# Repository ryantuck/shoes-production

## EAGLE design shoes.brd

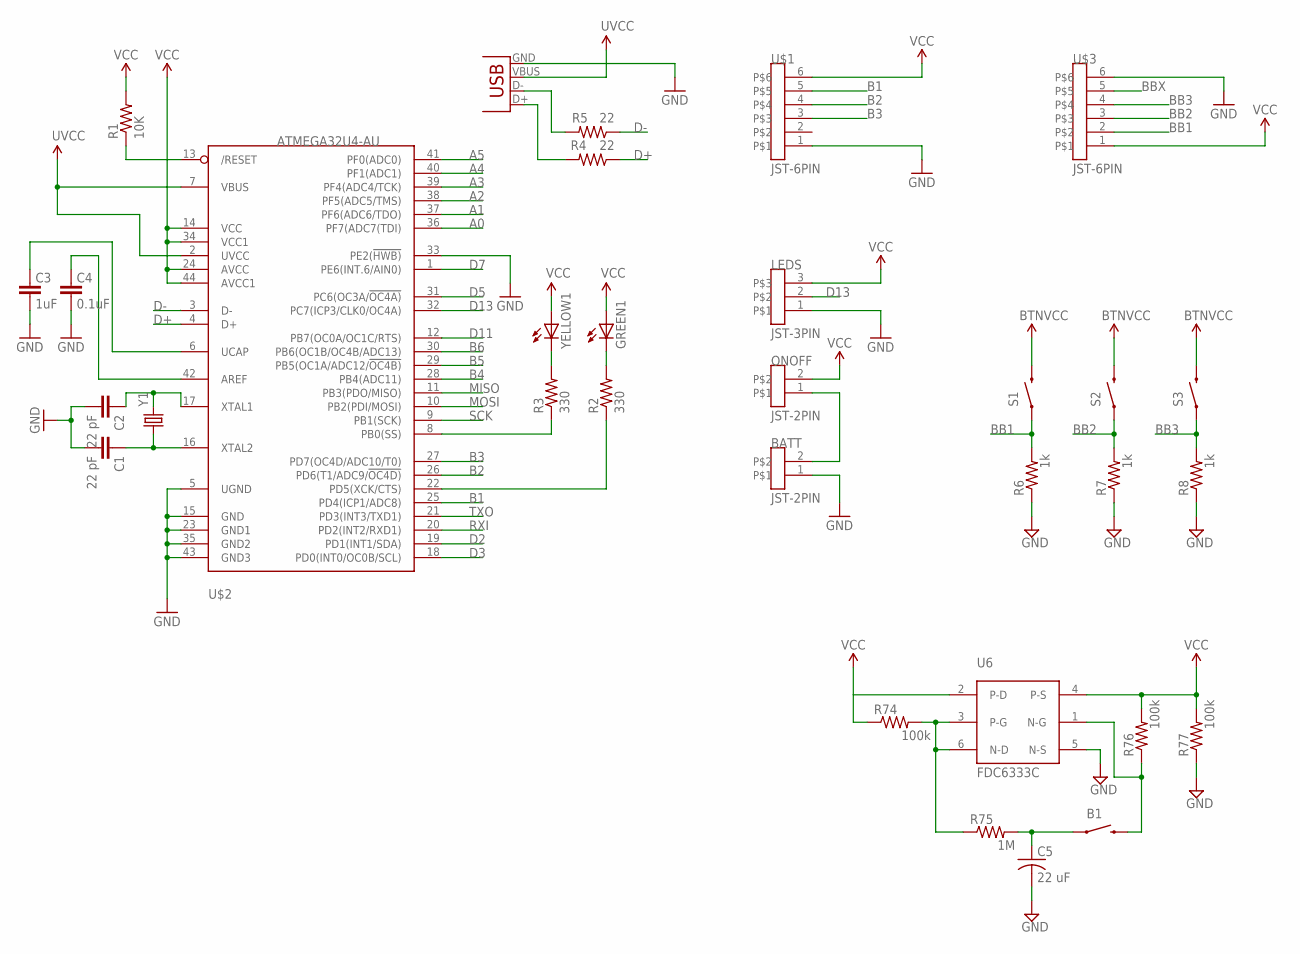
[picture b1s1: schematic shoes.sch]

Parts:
B1: SWITCH-MOMENTARY-2GULLWING; BUTTON-GULLWING
BATT: JST-2PIN; JST-PH-2
C1, C2: 22 pF; 0805
C3: 1uF; 0805
C4: 0.1uF; 0805
C5: 22 uF; 1206_P
GREEN1: LED; 0805_P
LEDS: JST-3PIN; JST-PH-3
ONOFF: JST-2PIN; JST-PH-2
R1: 10K; 0805
R2, R3: 330; 0805
R4, R5: 22; 0805
R6, R7, R8: 1k; 0805
R74, R76, R77: 100k; 0603
R75: 1M; 0603
S1, S2, S3: SWITCH-MOMENTARY-2GULLWING; BUTTON-GULLWING
U6: FDC6333C; SOT-23
U$1, U$3: JST-6PIN; JST-PH-6
U$2: ATMEGA32U4-AU; TQFP44
X2: USB-MICROB
Y1: CRYSTALHC49US; HC49US
YELLOW1: LED; 0805_P

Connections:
3.3V: R76.2, R77.2, U6.4 (P-S)
5V: GREEN1.NEG (A), LEDS.3, ONOFF.2, R1.2, U$1.6, U$2.14 (VCC), U$2.24 (AVCC), U$2.34 (VCC1), U$2.44 (AVCC1), YELLOW1.NEG (A)
A0: U$2.36 (PF7(ADC7(TDI))
A1: U$2.37 (PF6(ADC6/TDO))
A2: U$2.38 (PF5(ADC5/TMS))
A3: U$2.39 (PF4(ADC4/TCK))
A4: U$2.40 (PF1(ADC1))
A5: U$2.41 (PF0(ADC0))
B1: U$1.5, U$2.25 (PD4(ICP1/ADC8))
B2: U$1.4, U$2.26 (PD6(T1/ADC9/!OC4D))
B3: U$1.3, U$2.27 (PD7(OC4D/ADC10/T0))
B4: U$2.28 (PB4(ADC11))
B5: U$2.29 (PB5(OC1A/ADC12/!OC4B))
B6: U$2.30 (PB6(OC1B/OC4B/ADC13))
BB1: R6.POS (2), S1.A1 (1), U$3.2
BB2: R7.POS (2), S2.A1 (1), U$3.3
BB3: R8.POS (2), S3.A1 (1), U$3.4
BBX: U$3.5
BTNGND: R6.NEG (1), R7.NEG (1), R8.NEG (1), U$3.6
BTNVCC: S1.B1 (2), S2.B1 (2), S3.B1 (2), U$3.1
D2: U$2.19 (PD1(INT1/SDA))
D3: U$2.18 (PD0(INT0/OC0B/SCL))
D5: U$2.31 (PC6(OC3A/!OC4A))
D7: U$2.1 (PE6(INT.6/AIN0))
D11: U$2.12 (PB7(OC0A/OC1C/RTS))
D13: LEDS.2, U$2.32 (PC7(ICP3/CLK0/OC4A))
D14: R3.1, U$2.8 (PB0(SS))
D+: R4.1, U$2.4 (D+)
D-: R5.1, U$2.3 (D-)
GND: BATT.1, C1.POS (2), C2.POS (2), C3.1, C4.1, C5.2 (NEG), LEDS.1, R77.1, U6.5 (N-S), U$1.1, U$2.5 (UGND), U$2.15 (GND), U$2.23 (GND1), U$2.33 (PE2(!HWB)), U$2.35 (GND2), U$2.43 (GND3), X2.GND
MISO: U$2.11 (PB3(PDO/MISO))
MOSI: U$2.10 (PB2(PDI/MOSI))
unnamed: C2.NEG (1), U$2.17 (XTAL1), Y1.2
unnamed: R4.2, X2.D+
unnamed: R5.2, X2.D-
unnamed: C1.NEG (1), U$2.16 (XTAL2), Y1.1
unnamed: C4.2, U$2.42 (AREF)
unnamed: C3.2, U$2.6 (UCAP)
unnamed: R3.2, YELLOW1.POS (C)
unnamed: GREEN1.POS (C), R2.2
unnamed: B1.B1 (2), R76.1, U6.1 (N-G)
unnamed: R74.2, R75.1, U6.3 (P-G), U6.6 (N-D)
unnamed: B1.A1 (1), C5.1 (POS), R75.2
RESET1: R1.1, U$2.13 (/RESET)
RXI: U$2.20 (PD2(INT2/RXD1))
SCK: U$2.9 (PB1(SCK))
TXLED: R2.1, U$2.22 (PD5(XCK/CTS))
TXO: U$2.21 (PD3(INT3/TXD1))
UVCC: U$2.2 (UVCC), U$2.7 (VBUS), X2.VBUS
VIN: BATT.2, ONOFF.1, R74.1, U6.2 (P-D)

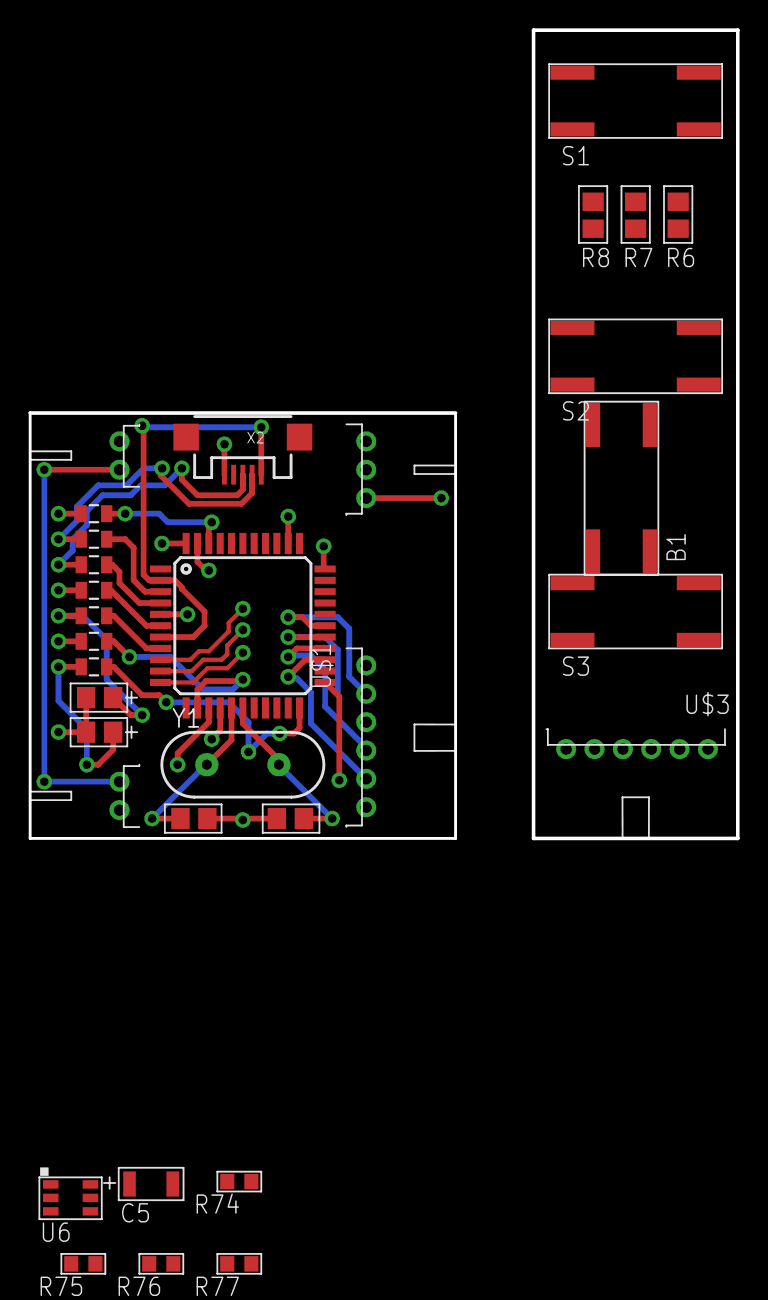
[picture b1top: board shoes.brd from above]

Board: 2 copper layers, 49.9 x 57.0 mm, 32 parts (0 on the bottom side), 30 nets.

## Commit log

2015-08-01 Production shoe PCBs

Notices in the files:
parts and their libraries:
SparkFun-Connectors: Licensing: CC v3.0 Share-Alike You are welcome to use this library for commercial purposes.
